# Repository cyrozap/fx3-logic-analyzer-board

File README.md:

# FX3 Logic Analyzer Board

## Introduction

This is a simple expansion board for the [Cypress FX3 SuperSpeed Explorer Kit (CYUSB3KIT-003)][kit] that turns it into a 16-channel, 100 MSps logic analyzer.

### Features

 - 16 input channels.
 - 100 MSps maxumim sample rate.
 - Supports logic levels of 1V8 and higher.
 - 5V tolerant inputs.
 - Connector pinout compatible with the [Digilent Analog Discovery][analog-discovery] and the [Analog Devices ADALM2000][adalm2000].
   - Cables can be purchased [here][cable], but the pin header has a standard 0.1 inch (2.54 mm) pitch, so any 0.1 inch pitch "dupont wire"/breadboard jumper wires will work.
 - Design suitable for manufacturing with budget/hobbyist PCB services.
   - 2 layers
   - 8-mil (0.2032 mm) minimum trace/space
   - 8-mil (0.2032 mm) minimum annular ring
   - 12-mil (0.3048 mm) minimum drill

## Images

[![A render of the front side of the PCB.][render-front]][render-front]
[![A render of the back side of the PCB.][render-back]][render-back]

## Errata

### v0.1

 - While the current design works, the return paths for the signal traces could use some improvement.
   Specifically, there should be ground paths routed either alongside or below each of the signal paths.
 - The input connector pinout should be labeled on the silkscreen.
 - The FX3 dev kit is a really tight fit, so the pin headers likely need to be moved a little closer together.
 - There currently isn't any kind of termination on the inputs, so sometimes for very fast signals the logic analyzer probe wires end up acting like stub wires and degrade the signal to the point that the Device Under Test (DUT) doesn't work properly.

## License

This project is released under the [Creative Commons Zero Public Domain Dedication][cc0], so please feel free to use or modify it however you like.

[kit]: https://www.cypress.com/documentation/development-kitsboards/cyusb3kit-003-ez-usb-fx3-superspeed-explorer-kit
[analog-discovery]: https://digilent.com/reference/test-and-measurement/analog-discovery/reference-manual#pin_out_diagram
[adalm2000]: https://wiki.analog.com/university/tools/m2k/devs/intro#pinout
[cable]: https://digilent.com/shop/2x15-flywires-signal-cable-assembly-for-the-analog-discovery/
[render-front]: doc/pcb-render-v0.1-front.png
[render-back]: doc/pcb-render-v0.1-back.png
[cc0]: https://creativecommons.org/publicdomain/zero/1.0/

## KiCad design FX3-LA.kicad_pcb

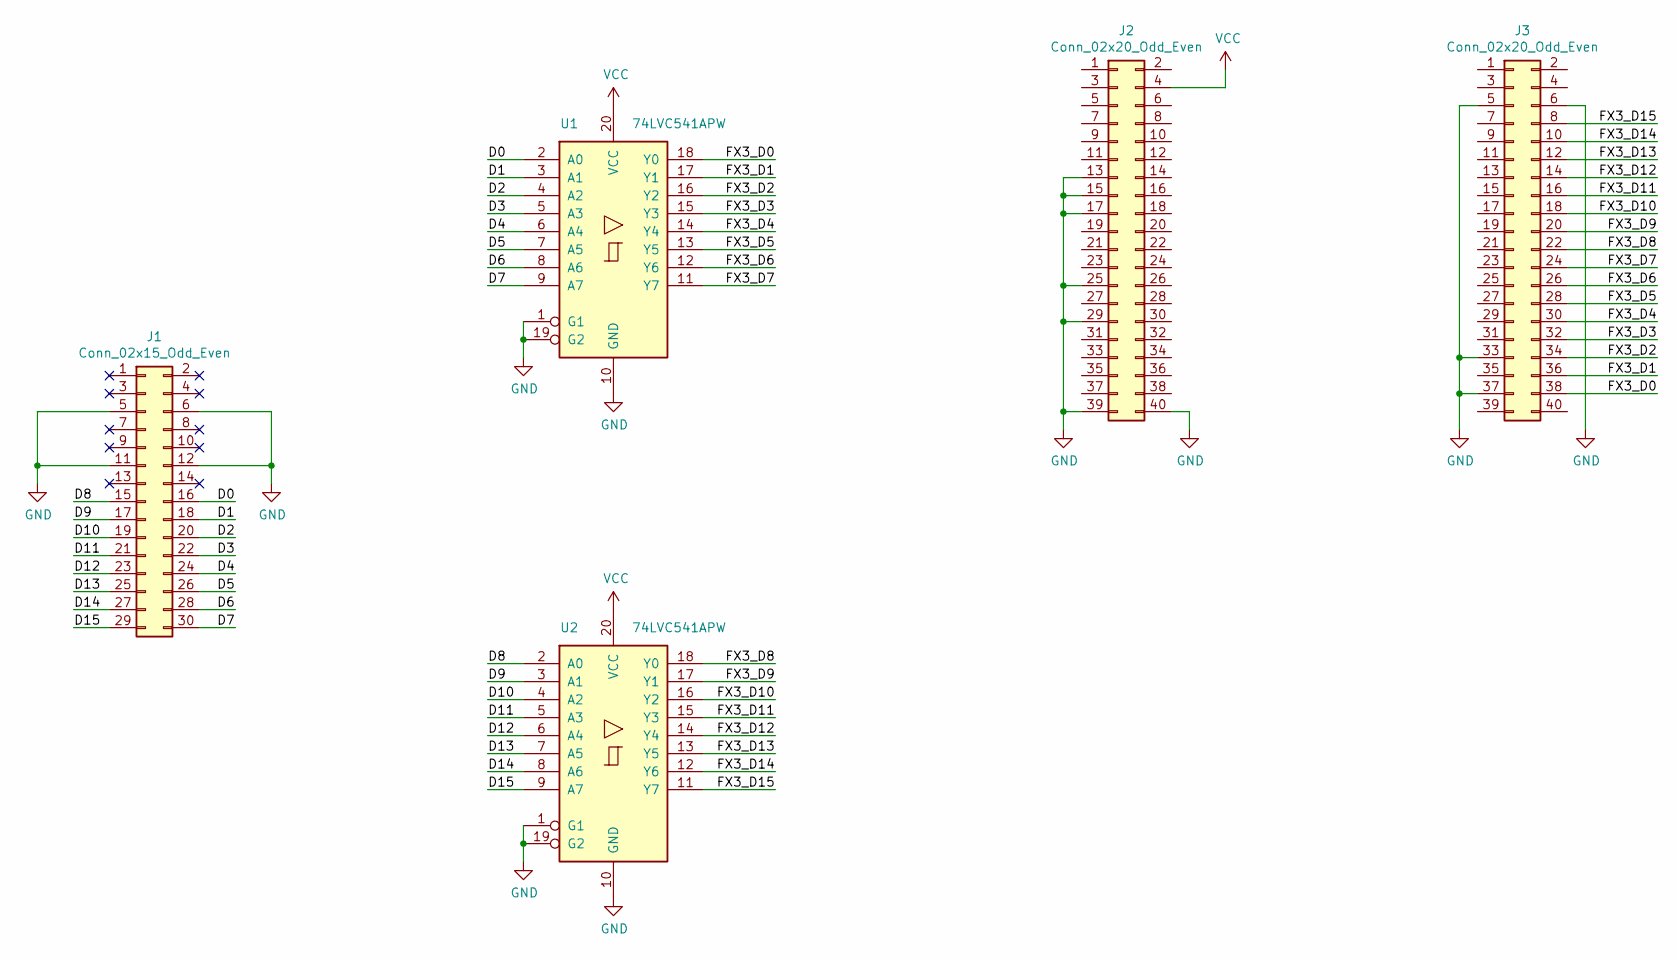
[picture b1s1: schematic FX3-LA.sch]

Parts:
J1: Conn_02x15_Odd_Even; PinHeader_2x15_P2.54mm_Vertical
J2, J3: Conn_02x20_Odd_Even; PinHeader_2x20_P2.54mm_Vertical
U1, U2: 74LVC541APW; TSSOP-20_4.4x6.5mm_P0.65mm

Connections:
/D0: J1.16, U1.2 (A0)
/D1: J1.18, U1.3 (A1)
/D2: J1.20, U1.4 (A2)
/D3: J1.22, U1.5 (A3)
/D4: J1.24, U1.6 (A4)
/D5: J1.26, U1.7 (A5)
/D6: J1.28, U1.8 (A6)
/D7: J1.30, U1.9 (A7)
/D8: J1.15, U2.2 (A0)
/D9: J1.17, U2.3 (A1)
/D10: J1.19, U2.4 (A2)
/D11: J1.21, U2.5 (A3)
/D12: J1.23, U2.6 (A4)
/D13: J1.25, U2.7 (A5)
/D14: J1.27, U2.8 (A6)
/D15: J1.29, U2.9 (A7)
/FX3_D0: J3.38, U1.18 (Y0)
/FX3_D1: J3.36, U1.17 (Y1)
/FX3_D2: J3.34, U1.16 (Y2)
/FX3_D3: J3.32, U1.15 (Y3)
/FX3_D4: J3.30, U1.14 (Y4)
/FX3_D5: J3.28, U1.13 (Y5)
/FX3_D6: J3.26, U1.12 (Y6)
/FX3_D7: J3.24, U1.11 (Y7)
/FX3_D8: J3.22, U2.18 (Y0)
/FX3_D9: J3.20, U2.17 (Y1)
/FX3_D10: J3.18, U2.16 (Y2)
/FX3_D11: J3.16, U2.15 (Y3)
/FX3_D12: J3.14, U2.14 (Y4)
/FX3_D13: J3.12, U2.13 (Y5)
/FX3_D14: J3.10, U2.12 (Y6)
/FX3_D15: J3.8, U2.11 (Y7)
GND: J1.5, J1.6, J1.11, J1.12, J2.13, J2.15, J2.17, J2.25, J2.29, J2.39, J2.40, J3.5, J3.6, J3.33, J3.37, U1.1 (G1), U1.10 (GND), U1.19 (G2), U2.1 (G1), U2.10 (GND), U2.19 (G2)
VCC: J2.4, U1.20 (VCC), U2.20 (VCC)

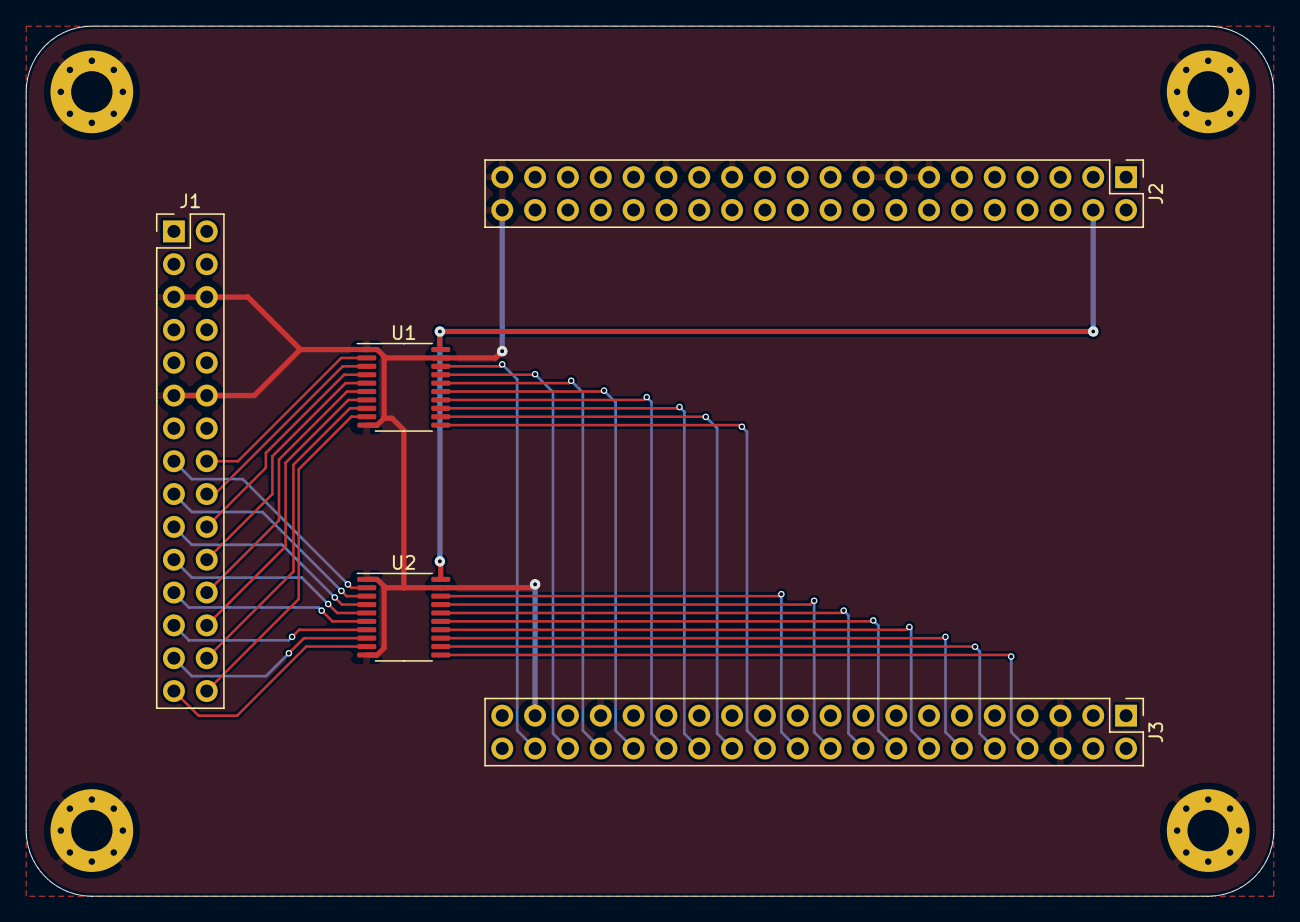
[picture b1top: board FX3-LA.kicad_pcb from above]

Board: 2 copper layers, 96.5 x 67.3 mm, 5 parts (0 on the bottom side), 34 nets.

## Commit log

2021-04-21 Initial commit of v0.1
2021-10-11 Add Readme with images
2021-10-11 Release under the CC0
